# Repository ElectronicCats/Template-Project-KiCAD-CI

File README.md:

# Plantilla para proyectos de ingeniería

Esta plantilla es la base para cualquier proyecto desarrollado en Electronic Cats.

Automáticamente, se generarán todos los archivos necesarios para la compra de material, fabricación y ensamble.

Así como documentos complementarios para un proyecto completo.

> Este README.md puede ser utilizado como plantilla para documentación, de esta manera se puede incluir generalidades, recomendaciones y todo lo necesario para entender el proyecto.

## ¿Cómo utilizar esta plantilla?

Para comenzar un nuevo proyecto, presiona el botón de "Use this template".

### KiCad

Para esta plantilla, el hardware debe de ser diseñado y/o desarrollado en KiCad 9.

Al término del diseño del proyecto, KiCad deberá de generar los siguientes archivos:

- nombre_del_proyecto.kicad_pro

- nombre_de_la_pcb.kicad_pcb

- nombre_del_esquematico.kicad_sch

Además de archivos temporales, los cuales Git ignora al momento de cualquier push.

[Archivos ignorados](.gitignore)

Estos archivos deberán ser guardados dentro de la carpeta de [hardware](hardware/).

### Configuración de automatización

Una vez terminado el proyecto, antes de hacer el primer Release, se deberán realizar algunos cambios para la automatización de archivos.

En la carpeta [.github/workflows](.github/workflows/) se encuentra el archivo kicad_kibot.yml, en donde los siguientes campos deberán ser modificados

```yaml

# optional - schematic file

schema: 'hardware/Template-KiCAD-Project-CI.kicad_sch'

# optional - pcb file

board: 'hardware/Template-KiCAD-Project-CI.kicad_pcb'

```

Se deberá reemplazar el nombre del archivo "Template-KiCAD-Project-CI" por el nombre del proyecto diseñado.

Es importante conservar las extensiones de archivo .kicad_sch y .kicad_pcb.

### Activar/desactivar DRC y ERC

Las opciones de DRC y ERC están siempre activas predeterminadamente, para desactivarlas se deberá de eliminar las siguientes líneas del archivo [electroniccats_sch.kibot.yaml](hardware/electroniccats_sch.kibot.yaml).

```yaml

run_erc: true

run_drc: true

```

Esta acción solo correrá cada vez que se haga un release.

Si, además, se busca desactivar el DRC y el ERC cuando se haga push o pull request, es necesario eliminar el archivo [action_drc.yml](.github/workflows/action_drc.yml).

## Creación de Release

Al terminar el proyecto y su revisión, se publicará el primer Release.

Para crear un nuevo Release, presiona el botón de "Create a new release".

Una vez creado el Release, podrás ver la creación de los archivos en la sección de Actions.

Al terminar, los archivos serán generados en el mismo release.

## Elementos para mejorar tu `Readme.md`

Los archivos `Readme.md` se crean con el propósito de hacer visualmente agradable un repositorio para los usuarios que visiten nuestro proyecto, puedes utilizar algunos de los siguientes elementos.

### Código
Quoting code, como lo dice su nombre, se utiliza para añadir código y que se separe del texto plano. Debes de agregar el codigo dentro de ` ``` ```` ` , ademas si agregas el nombre del lenguaje inmediatamente despues de las primeras ` ``` ` las funciones se pondran de color diferenciandolas del resto del codigo. Aquí algunos ejemplos. Puedes encontrar los lenguajes aquí:
https://github.com/github/linguist/blob/master/vendor/README.md
```sh
192.168.0.1
cd Downloads
```
  ```diff
- text in red
+ text in green
! text in orange
# text in gray
@@ text in purple (and bold)@@
```

### Hipervínculos

Usa hipervínculos o links para redirigir a los usuarios a páginas donde puedan conocer más acerca de algún tema o concepto en concreto, hay dos formas de hacer esto:

- [Agregando el link en seguida](https://github.com/ElectronicCats/Template-Project-KiCAD-CI) - Con esta forma deberas de seguir el siguiente formato `[Texto](www.url.com)`. El texto que se mostrará en la página principal del Readme será el que se encuentra dentro de los corchetes y el link de la página deberá de ir de manera inmediata a los corchetes dentro de paréntesis.

- [Agregando el link como referencia] - Al igual que otro tipo de formatos de referencia en este agregas el texto que se mostrará en la página principal del repositorio dentro de corchetes `[Texto]` y al final de tu archivo (de preferencia) agregas la referencia de la siguiente manera: `[Texto]:<www.url.com>`, este no se mostrara en el archivo por lo que es una buena forma de mantener un formato y un orden.  

### Tablas

Las tablas que todos conocemos con filas y columnas. El formato para estas tablas se basa en el uso del símbolo `|`, entonces debes de encerrar las palabras como esto: `|Columna1|` (sin la posibilidad de dos | seguidos), para agregar más columnas basta con dar un espacio y repetir el formato, sin embargo, para añadir filas debes de hacer un salto de línea y repetir el formato de columnas, dejándonos una tabla como la siguiente:

|Columna1|Columna2|
|-|-|
|Fila 1 Columna 1|Fila 2 Columna 2|

Nota: Si agregas en la segunda fila guiones (-) harás que la primera fila se convierta en el encabezado de la tabla.

### Imágenes
Puedes añadir imágenes siempre y cuando estas estén en Internet, si quieres agregar una nueva imagen tambien la puedes arrastrar y soltar en el cuadro de texto (en caso de que edites tu `Readme.md`) directo desde GitHub, esto hará que se guarde tu imagen en una carpeta oculta dentro de tu repositorio.
El formato para agregar imagenes es: ``
Si requieres que al hacer click en tu imagen se redirija a otra pagina usa el siguiente formado ``
Es importante agregar `https://` , si no te enviara a una página de GitHub que probablemente no exista.

### Referencias
Es posible que en la wiki hayas visto numeritos como este --->[^1], pero que significan?

No son más que referencias que puedes hacer para hacer saltos de información e ir directo a la referencia haciendo click en el pequeño número.
[^1]: Soy la referencia :))))

### Emojis :trollface: :shipit:
Solo escribe el código del emoji así: `:EMOJICODE:`.
Aqui la lista de los [EMOJICODEs](https://github.com/ikatyang/emoji-cheat-sheet/blob/master/README.md#github-custom-emoji)

### Listas con checkbox
Usa este formato:
```
- [x] GFM task list 1
- [x] GFM task list 2
- [ ] GFM task list 3
    - [ ] GFM task list 3-1
    - [ ] GFM task list 3-2
    - [ ] GFM task list 3-3
- [ ] GFM task list 4
    - [ ] GFM task list 4-1
    - [ ] GFM task list 4-2
  ```
  Y tendras algo asi: 
- [x] GFM task list 1
- [x] GFM task list 2
- [ ] GFM task list 3
    - [ ] GFM task list 3-1
    - [ ] GFM task list 3-2
    - [ ] GFM task list 3-3
- [ ] GFM task list 4
    - [ ] GFM task list 4-1
    - [ ] GFM task list 4-2

### Otros Elementos

Este tipo de indicadores nos pueden ayudar a identificar diferente información relacionada al proyecto, solo los debes de agregar como una imagen y en el URL  pegar el link correspondiente. 
Los ejemplos de arriba fueron generados con la pagina: Shields.io , solo debes de asegurarte que son para GitHub y que tienen el formato `MarkDown`

- Badges,
En caso de que necesites algun referente a alguna empresa o plataforma puedes usar esta pagina: https://dev.to/envoy_/150-badges-for-github-pnk

- Estadísticas
Utilizando el projecto de este usuario puedes agregar estadísticas del proyecto como estas:

https://github.com/anuraghazra/github-readme-stats

**NOTA**:Son pocas las tarjetas que puedes utilizar con el proyecto de este usuario para repositorios ya que son más dirigidos a perfiles de GitHub.
 
## Maintainer

Electronic Cats invests time and resources providing this open source design, please support Electronic Cats and open-source hardware by purchasing products from Electronic Cats!

[Agregando el link como referencia]: <https://github.com/ElectronicCats/Template-Project-KiCAD-CI>

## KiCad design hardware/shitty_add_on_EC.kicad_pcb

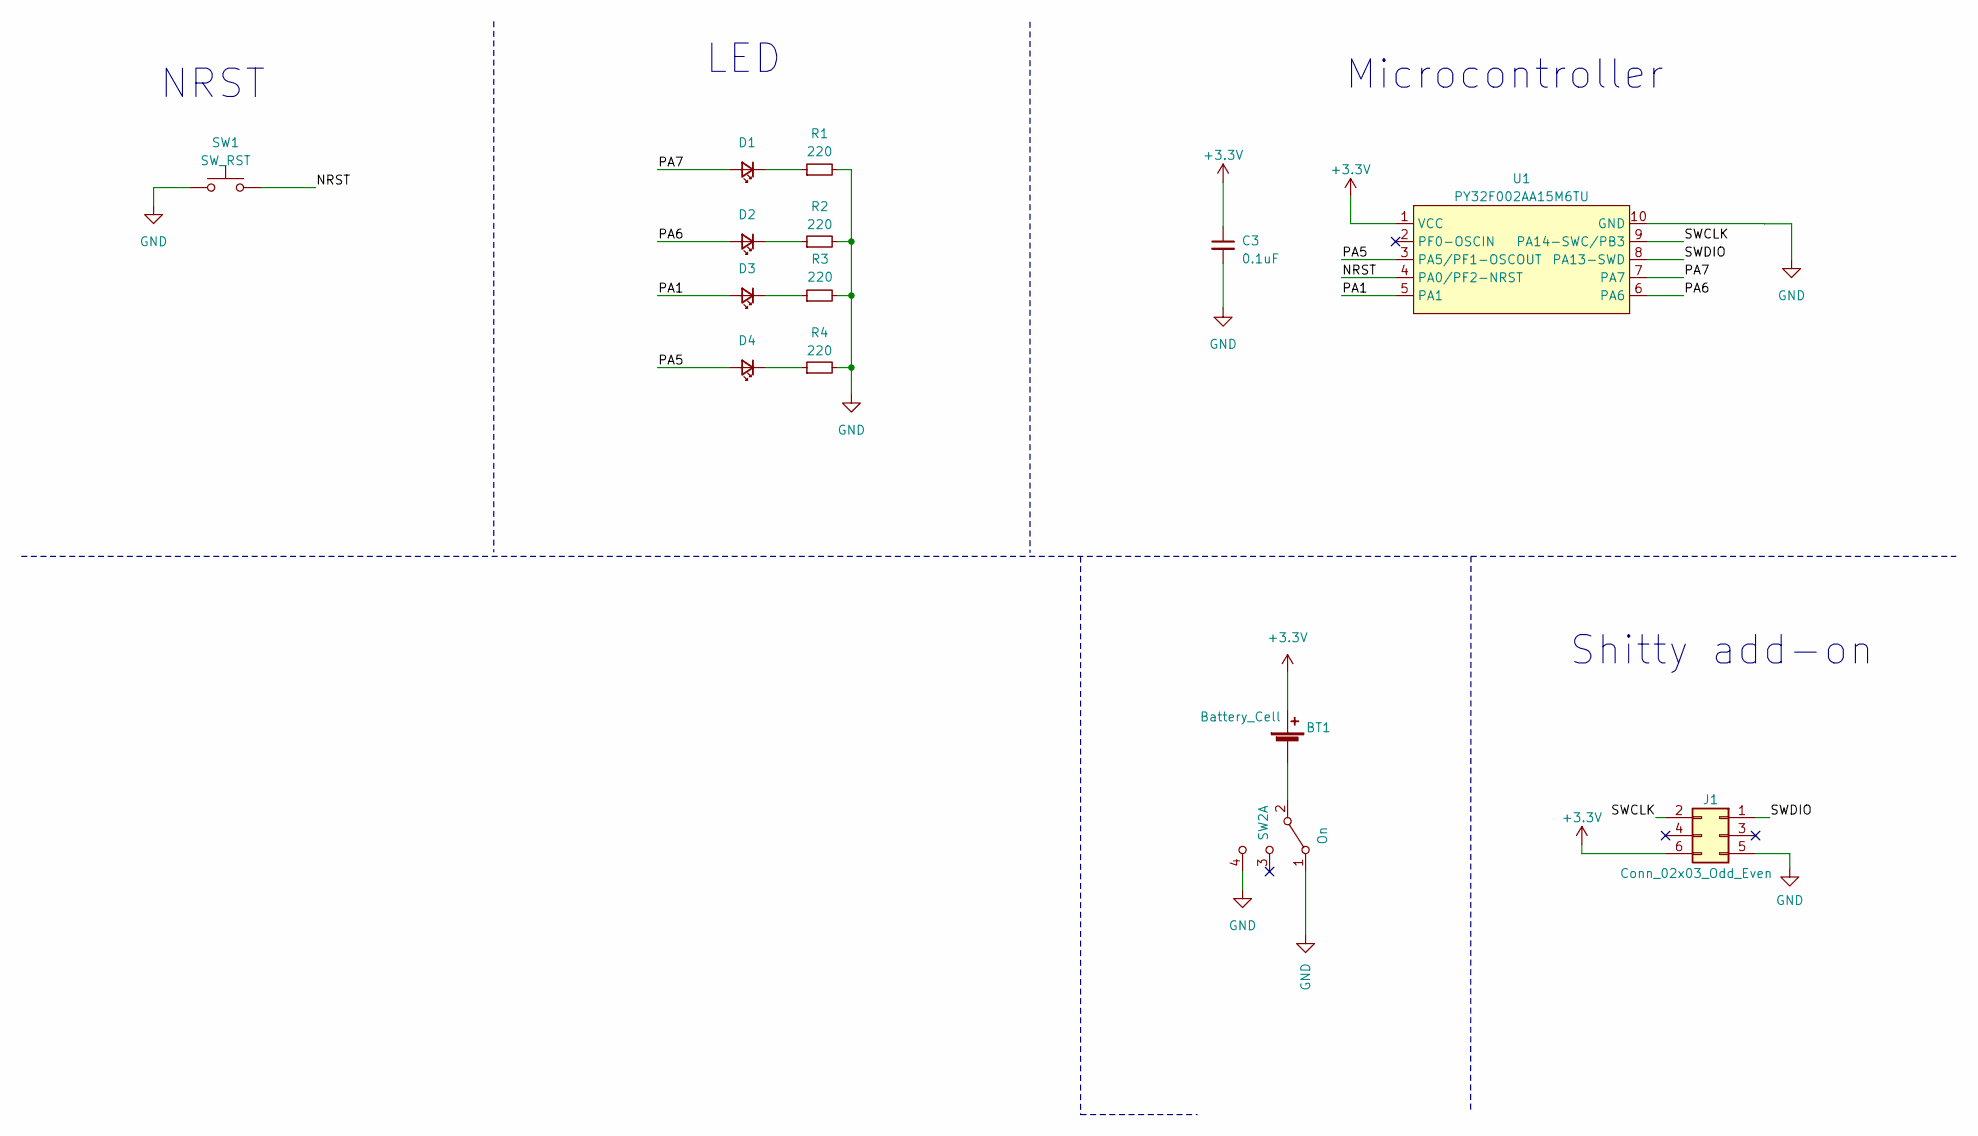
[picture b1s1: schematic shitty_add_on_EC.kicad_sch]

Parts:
BT1: Battery_Cell; BAT-HLD-001; LCSC# C964833
C3: 0.1uF; C_0603_1608Metric; LCSC# C478888
D1, D2, D3, D4: LED_Small; LYT77K-K2M1
J1: Conn_02x03_Odd_Even; B-2100N06P-B111_CKM; LCSC# C124390
R1, R2, R3, R4: 220; R_0805_2012Metric; LCSC# C22962
SW1: SW_RST; SW_SPST_TL3342; LCSC# C318889
SW2: On; MSK12C02; LCSC# C431540
U1: PY32F002AA15M6TU; PY32F002AA15M; LCSC# C5292058

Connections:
+3.3V: BT1.2 (+), J1.6, U1.1 (VCC); also elsewhere on the board
/NRST: SW1.2, U1.4 (PA0/PF2-NRST)
/PA1: D3.2 (A), U1.5 (PA1)
/PA5: D4.2 (A), U1.3 (PA5/PF1-OSCOUT)
/PA6: D2.2 (A), U1.6 (PA6)
/PA7: D1.2 (A), U1.7 (PA7)
/SWCLK: J1.2, U1.9 (PA14-SWC/PB3)
/SWDIO: J1.1, U1.8 (PA13-SWD)
GND: J1.5, R1.2, R2.2, R3.2, R4.2, SW1.1, SW2.1 (A), SW2.4 (C), U1.10 (GND); also elsewhere on the board
unnamed: BT1.1 (-), SW2.2 (B)
unnamed: D1.1 (K), R1.1
unnamed: D2.1 (K), R2.1
unnamed: D3.1 (K), R3.1
unnamed: D4.1 (K), R4.1

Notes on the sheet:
Microcontroller
NRST
Shitty add-on
LED

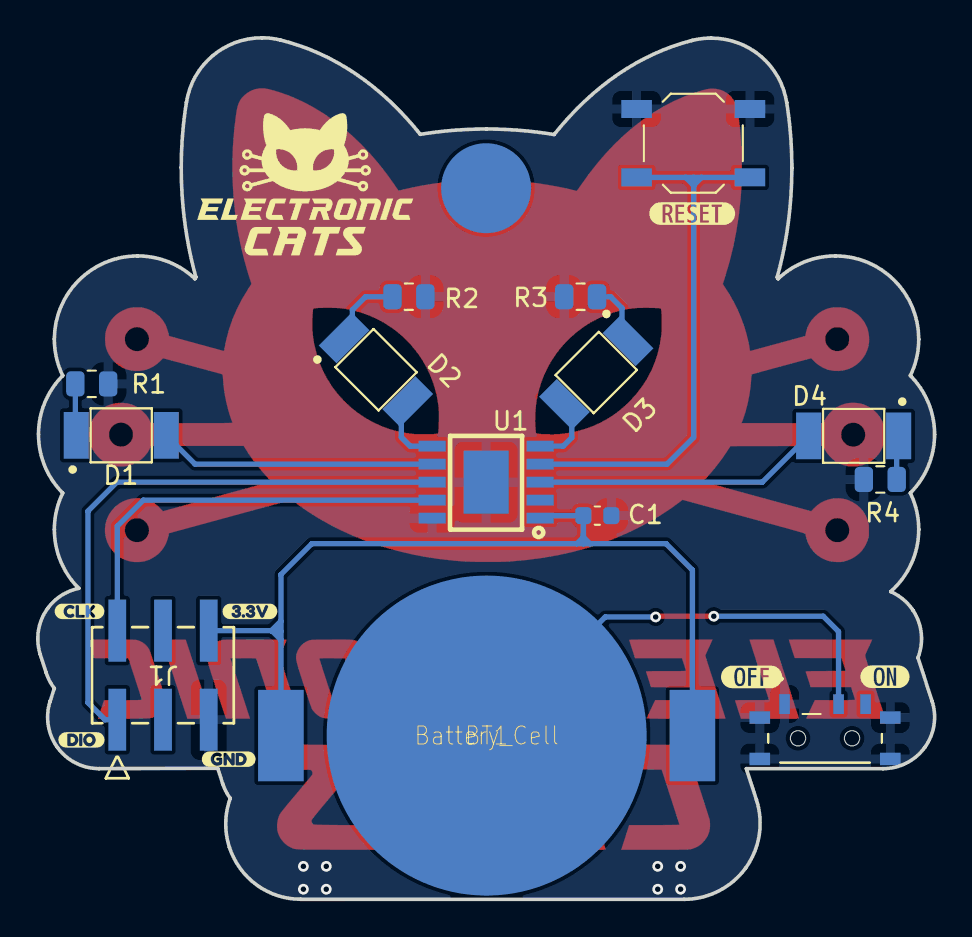
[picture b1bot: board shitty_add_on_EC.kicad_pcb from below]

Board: 2 copper layers, 49.8 x 47.9 mm, 22 parts (21 on the bottom side), 14 nets.

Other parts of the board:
C1: 0.1uF; C_0603_1608Metric
Ref**: Val**; BADGE ELECTRONIC CATS_NUEVO AJUSTE
kibuzzard-6814F9B5: G***; kibuzzard-6814F9B5
kibuzzard-6814F958: G***; kibuzzard-6814F958
kibuzzard-6814F974: G***; kibuzzard-6814F974
kibuzzard-6814F994: G***; kibuzzard-6814F994
kibuzzard-6818FBDE: G***; kibuzzard-6818FBDE
kibuzzard-6818FC11: G***; kibuzzard-6818FC11
kibuzzard-681900B7: G***; kibuzzard-681900B7

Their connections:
+3.3V: C1.1; also elsewhere on the board
GND: C1.2; also elsewhere on the board

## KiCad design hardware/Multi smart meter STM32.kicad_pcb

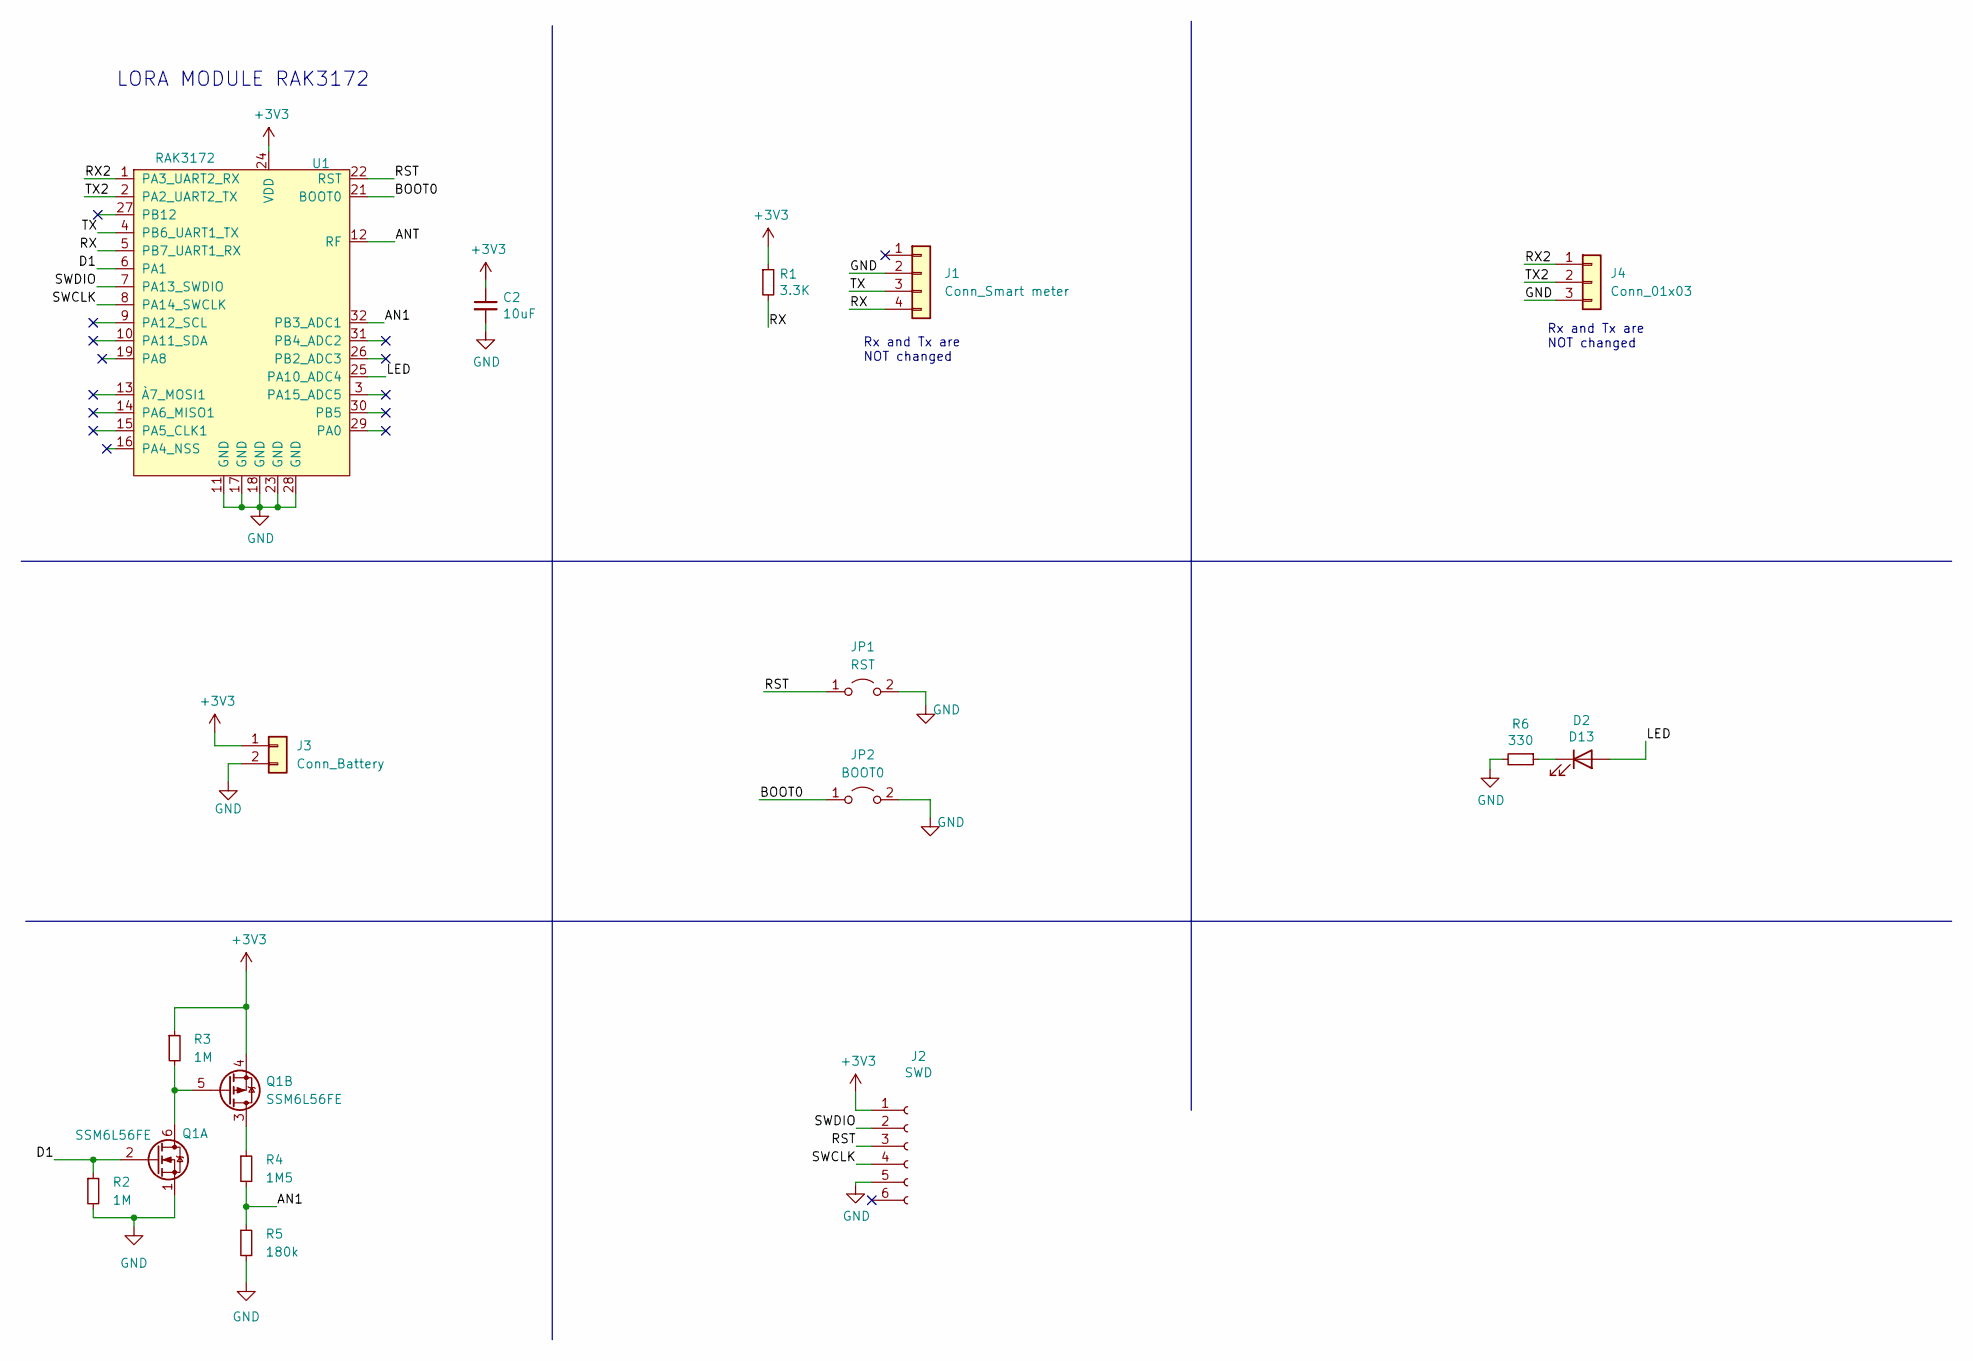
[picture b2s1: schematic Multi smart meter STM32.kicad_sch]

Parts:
C2: 10uF; C_0603_1608Metric
D2: D13; LED_0603_1608Metric_Pad1.05x0.95mm_HandSolder
J1: Conn_Smart meter; PinSocket_1x04_P2.54mm_Vertical
J2: SWD; Tag-Connect_TC2030-IDC-NL_2x03_P1.27mm_Vertical
J3: Conn_Battery; PinSocket_1x02_P2.54mm_Vertical
J4: Conn_01x03; PinSocket_1x03_P2.54mm_Vertical
JP1: RST; SolderJumper-2_P1.3mm_Open_Pad1.0x1.5mm
JP2: BOOT0; SolderJumper-2_P1.3mm_Open_Pad1.0x1.5mm
Q1: SSM6L56FE; SOTFL50P160X60-6N
R1: 3.3K; R_0603_1608Metric
R2, R3: 1M; R_0603_1608Metric
R4: 1M5; R_0603_1608Metric
R5: 180k; R_0603_1608Metric
R6: 330; R_0603_1608Metric
U1: RAK3172

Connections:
+3V3: C2.1, J2.1, J3.1, R1.1, U1.24 (VDD)
/AN1: R4.2, R5.1, U1.32 (PB3_ADC1)
/ANT: U1.12 (RF)
/BOOT0: JP2.1 (A), U1.21 (BOOT0)
/D1: Q1.2 (GN), R2.1, U1.6 (PA1)
/LED: D2.2 (A), U1.25 (PA10_ADC4)
/RST: J2.3, JP1.1 (A), U1.22 (RST)
/RX: J1.4, R1.2, U1.5 (PB7_UART1_RX)
/RX2: J4.1, U1.1 (PA3_UART2_RX)
/SWCLK: J2.4, U1.8 (PA14_SWCLK)
/SWDIO: J2.2, U1.7 (PA13_SWDIO)
/TX: J1.3, U1.4 (PB6_UART1_TX)
/TX2: J4.2, U1.2 (PA2_UART2_TX)
GND: C2.2, J1.2, J2.5, J3.2, J4.3, JP1.2 (B), JP2.2 (B), Q1.1 (SN), R2.2, R5.2, R6.2, U1.11 (GND), U1.17 (GND), U1.18 (GND), U1.23 (GND), U1.28 (GND)
unnamed: D2.1 (K), R6.1
unnamed: Q1.3 (DP), R4.1
unnamed: Q1.4 (SP), R3.1
unnamed: Q1.5 (GP), Q1.6 (DN), R3.2

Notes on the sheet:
Rx and Tx are NOT changed
LORA MODULE RAK3172

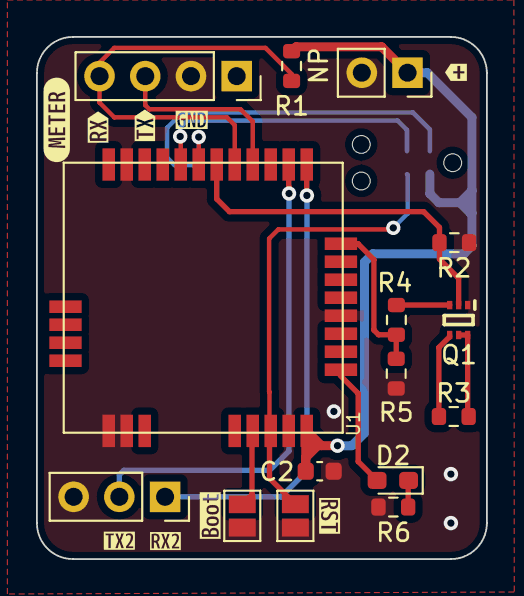
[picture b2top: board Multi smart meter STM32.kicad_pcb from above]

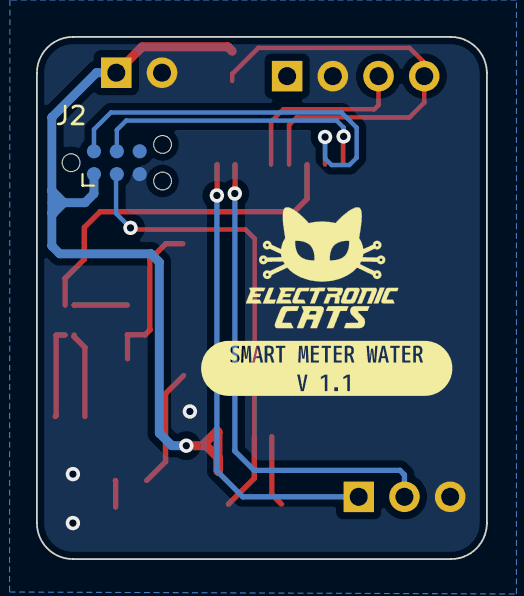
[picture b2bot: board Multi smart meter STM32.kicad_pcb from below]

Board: 2 copper layers, 25.0 x 29.0 mm, 26 parts (2 on the bottom side), 17 nets.

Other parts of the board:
kibuzzard-62E97AD3: G***; kibuzzard-62E97AD3
kibuzzard-62E99D3D: G***; kibuzzard-62E99D3D
kibuzzard-62E965C8: G***; kibuzzard-62E965C8
kibuzzard-62E977A3: G***; kibuzzard-62E977A3
kibuzzard-62E977DB: G***; kibuzzard-62E977DB
kibuzzard-62E977FF: G***; kibuzzard-62E977FF
kibuzzard-62E9673C: G***; kibuzzard-62E9673C
kibuzzard-62E9772E: G***; kibuzzard-62E9772E
kibuzzard-62E9777B: G***; kibuzzard-62E9777B
kibuzzard-62E96745: G***; kibuzzard-62E96745

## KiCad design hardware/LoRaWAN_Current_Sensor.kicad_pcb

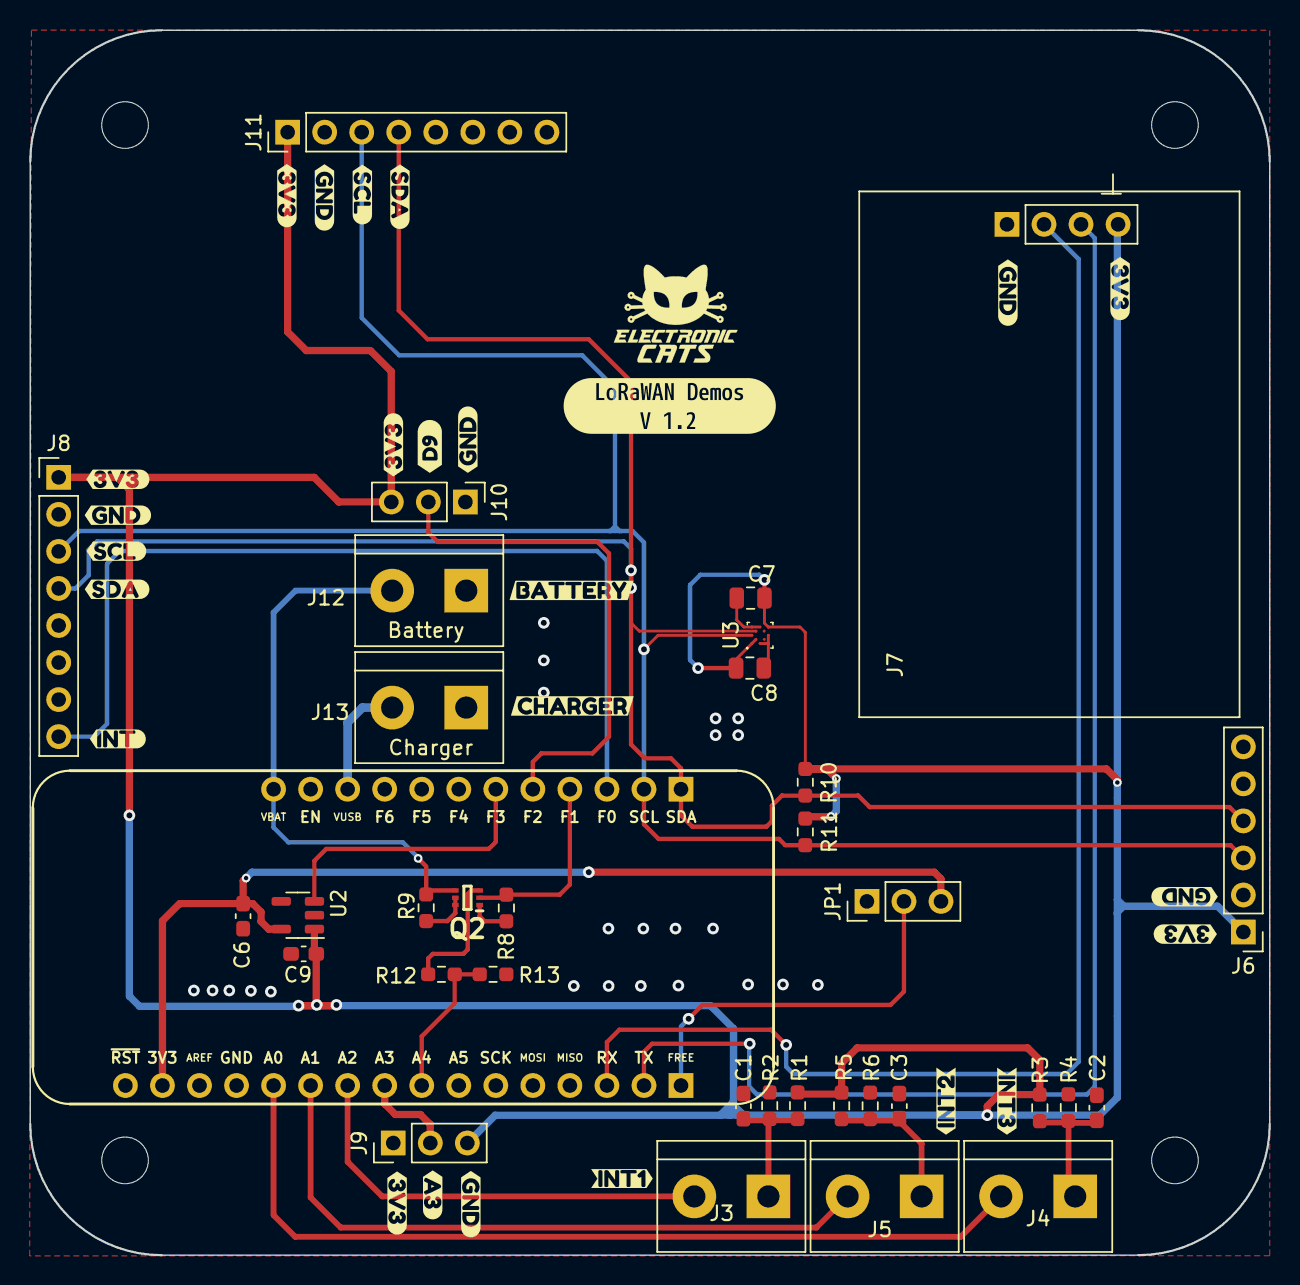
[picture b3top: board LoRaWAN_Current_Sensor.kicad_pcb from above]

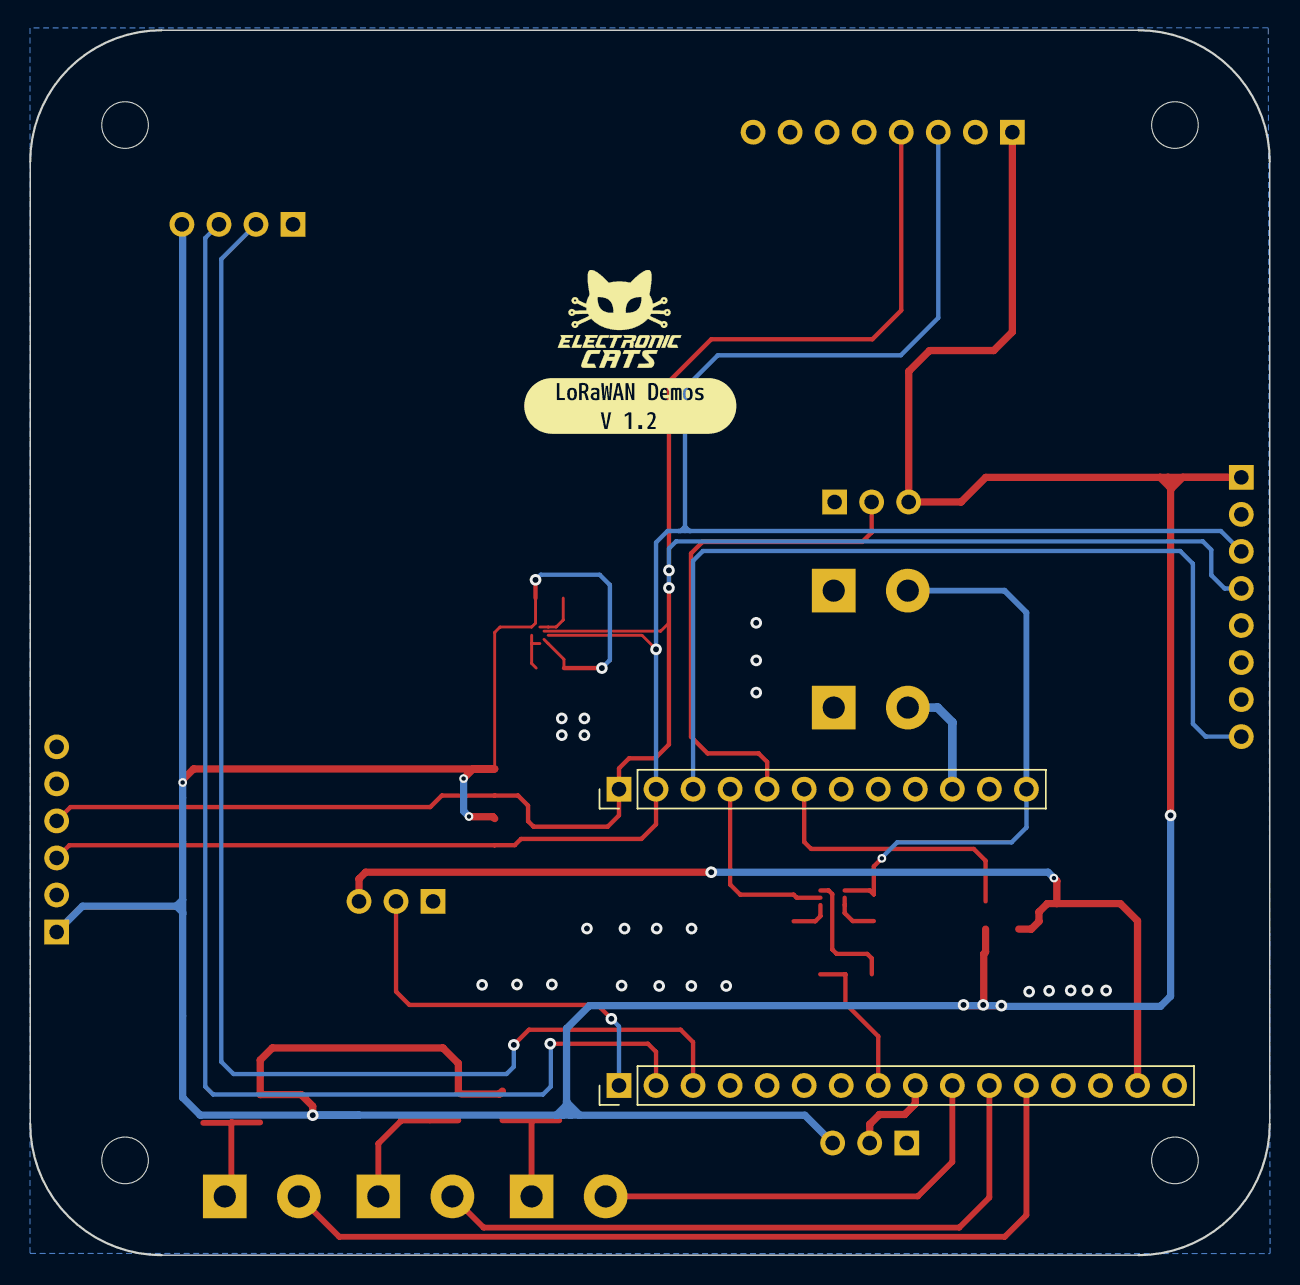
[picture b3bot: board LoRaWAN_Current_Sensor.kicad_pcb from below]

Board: 2 copper layers, 85.0 x 84.0 mm, 62 parts (3 on the bottom side), 24 nets.

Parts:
C1, C2, C3: 0.1nF; C_0603_1608Metric_Pad1.08x0.95mm_HandSolder
C6: 10uF; C_0603_1608Metric_Pad1.08x0.95mm_HandSolder
C7, C8: 100nF; C_0805_2012Metric
C9: 0.1 uF; C_0603_1608Metric_Pad1.08x0.95mm_HandSolder
J1: feather long; PinHeader_1x16_P2.54mm_Vertical
J2: feather short; PinHeader_1x12_P2.54mm_Vertical
J3, J4, J5: Singnal_IN; TerminalBlock_bornier-2_P5.08mm
J6: BME280; PinHeader_1x06_P2.54mm_Vertical
J7: GPS; PinHeader_1x04_P2.54mm_Vertical
J8: MPU; PinHeader_1x08_P2.54mm_Vertical
J9: Maxsonar; PinHeader_1x03_P2.54mm_Vertical
J10: DS18B20; PinHeader_1x03_P2.54mm_Vertical
J11: CJMCU 811; PinHeader_1x08_P2.54mm_Vertical
J12: Battery; TerminalBlock_bornier-2_P5.08mm
J13: Charger; TerminalBlock_bornier-2_P5.08mm
JP1: BOOT; PinHeader_1x03_P2.54mm_Vertical
Q2: SSM6L56FE; SOTFL50P160X60-6N
R1, R2, R3, R4, R5, R6: 10K; R_0603_1608Metric_Pad0.98x0.95mm_HandSolder
R8, R9: 1M; R_0603_1608Metric_Pad0.98x0.95mm_HandSolder
R10, R11: 4.7K; R_0603_1608Metric_Pad0.98x0.95mm_HandSolder
R12: 1M5; R_0603_1608Metric_Pad0.98x0.95mm_HandSolder
R13: 180k; R_0603_1608Metric_Pad0.98x0.95mm_HandSolder
U2: TCK106AF; SOT-23-5
U3: BMM150; WLCSP-12_1.56x1.56mm_P0.4mm
kibuzzard-61FC2E8E: G***; kibuzzard-61FC2E8E
kibuzzard-61FC2E76: G***; kibuzzard-61FC2E76
kibuzzard-61FC2EA4: G***; kibuzzard-61FC2EA4
kibuzzard-61FC2EC7: G***; kibuzzard-61FC2EC7
kibuzzard-61FC2ED7: G***; kibuzzard-61FC2ED7
kibuzzard-61FC2F42, kibuzzard-61FC2F42#2, kibuzzard-61FC2F42#3, kibuzzard-61FC2F42#4, kibuzzard-61FC2F42#5: G***; kibuzzard-61FC2F42
kibuzzard-61FC2F50, kibuzzard-61FC2F50#2, kibuzzard-61FC2F50#3, kibuzzard-61FC2F50#4, kibuzzard-61FC2F50#5: G***; kibuzzard-61FC2F50
kibuzzard-61FC30A8, kibuzzard-61FC30A8#2: G***; kibuzzard-61FC30A8
kibuzzard-61FC30B6: G***; kibuzzard-61FC30B6
kibuzzard-61FC30F1: G***; kibuzzard-61FC30F1
kibuzzard-61FC30FD: G***; kibuzzard-61FC30FD
kibuzzard-61FC3098, kibuzzard-61FC3098#2: G***; kibuzzard-61FC3098
kibuzzard-61FC3113: G***; kibuzzard-61FC3113
kibuzzard-62DACF23: G***; kibuzzard-62DACF23
kibuzzard-62DEB85D: G***; kibuzzard-62DEB85D
kibuzzard-62DEB877: G***; kibuzzard-62DEB877

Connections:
+3.3VP: C7.1, C8.1, C9.1, J6.1, J7.1, J8.1, J9.3, J10.3, J11.1, R1.1, R3.1, R5.1, R10.2, R11.2, U2.1 (OUT), U3.A1 (PS), U3.B2 (VDDIO), U3.E5 (VDD)
+3V3: C6.1, J1.15, JP1.3 (B), U2.5 (IN)
+BATT: J2.12, J12.2, Q2.4 (SP), R9.1
/A3: J1.9, J9.2
/A4: J1.8, R12.2, R13.1
/BOOT: J1.1, JP1.2 (C)
/D9: J2.5, J10.2
/D10: J2.4, Q2.2 (GN), R8.1
/IN2+: C3.1, J5.1, R5.2, R6.1
/IN2-: J1.11, J5.2
/IN3+: C2.1, J4.1, R3.2, R4.1
/IN3-: J1.12, J4.2
/IN+: C1.1, J3.1, R1.2, R2.1
/IN-: J1.10, J3.2
/INT: J2.3, J8.8
/RX: J1.3, J7.3
/SCL: J2.2, J6.3, J8.3, J11.3, R11.1, U3.A3 (SCK)
/SDA: J2.1, J6.4, J8.4, J11.4, R10.1, U3.B4 (SDI)
/TX: J1.2, J7.2
/VCC_EN: J2.6, U2.3 (CRTL)
GND: C1.2, C2.2, C3.2, C6.2, C7.2, C8.2, C9.2, J1.13, J6.2, J7.4, J8.2, J9.1, J10.1, J11.2, J11.5, J12.1, J13.1, JP1.1 (A), Q2.1 (SN), R2.2, R4.2, R6.2, R8.2, R13.2, U2.2 (GND), U3.A5 (CSB), U3.C1 (SDO), U3.C5 (GND), U3.E1 (GND), U3.E3 (GND)
unnamed: Q2.3 (DP), R12.1
unnamed: Q2.5 (GP), Q2.6 (DN), R9.2
VBUS: J2.10, J13.2

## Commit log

2022-08-15 add example project
2022-08-15 Init script github action
2022-08-15 active kicad6
2022-08-15 add Kibot config file
2022-08-15 Update paths
2022-08-15 fix typo
2022-08-15 add files
2022-08-15 rename config file
2022-08-15 deactive drc
2022-08-15 Add schematic example
2022-08-22 rename description file
2022-08-23 Added branch testing and release trigger
2022-08-23 Added pcb and sch config files and readme template updated
2022-08-23 Fixed release trigger
2022-08-23 Fixed config file name
2022-08-23 Fixed jobs
2022-08-23 Fixed sch config file
2022-08-23 path test
2022-08-23 path update
2022-08-24 Added sch path
2022-08-24 Fixed wrong bot config
2022-08-24 Added new examples
2022-08-24 Fixed hw path
2022-08-24 Fixed examples and path
2022-08-24 Fixed path
2022-08-24 Fixed bot version
2022-08-24 Deleted html bom
2022-08-24 Fixed csv and xlsx file gen
2022-08-24 Fixed upload artifacts
2022-08-24 Fixed upload path
2022-08-25 added upload assets
2022-08-25 fixed upload assets
2022-08-25 fixed assets files
2022-08-25 test path
2022-08-25 more assets
2022-08-25 fixed assets path
2022-08-25 added extra assets
2022-08-25 guide added and fixed zip files
2022-08-25 fixed JLCPCB path
2022-08-25 added new workflow
2022-09-30 Create Stale config
2022-10-18 Improved csv grouping, modified readme.md
2022-10-19 readme updated and csv format rearranged
2024-06-27 chore: update temporary and exported bom files
2025-11-23 feat: update kicad 9
2025-11-23 feat: run with change yml files
2025-11-23 docs: rename files
2025-11-23 docs: update README
2025-11-23 feat: caché, validación y manejo de errores
2025-11-26 fet: only update version
2025-11-26 CI: update trigger action
2025-11-26 doc: update v9
2025-11-26 CI: add cache
2025-11-26 CI:rename fles
2025-11-26 feat: temporal project
2025-11-26 CI: add file config
2025-11-26 CI: fix fiel and warnig deprecated
2025-11-26 CI: find file
2025-11-26 CI: add reports
2025-11-26 CI: find files fabrication
2025-11-26 CI: find files
2025-11-26 CI: gitignore generico
2025-11-26 CI: fix path
2025-11-26 CI: update
2025-11-26 CI: test
2025-11-26 CI: other test
2025-11-26 CI: if for releases
2025-11-26 CI: only file for CI
2025-11-26 feat: remove project example
